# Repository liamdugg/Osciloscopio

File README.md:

# Osciloscopio

Proyecto TDII - 2022

Osciloscopio para señales audibles

Integrantes
  - Contreras, Nahuel
  - Duggan, Liam
  - Ochoa, David

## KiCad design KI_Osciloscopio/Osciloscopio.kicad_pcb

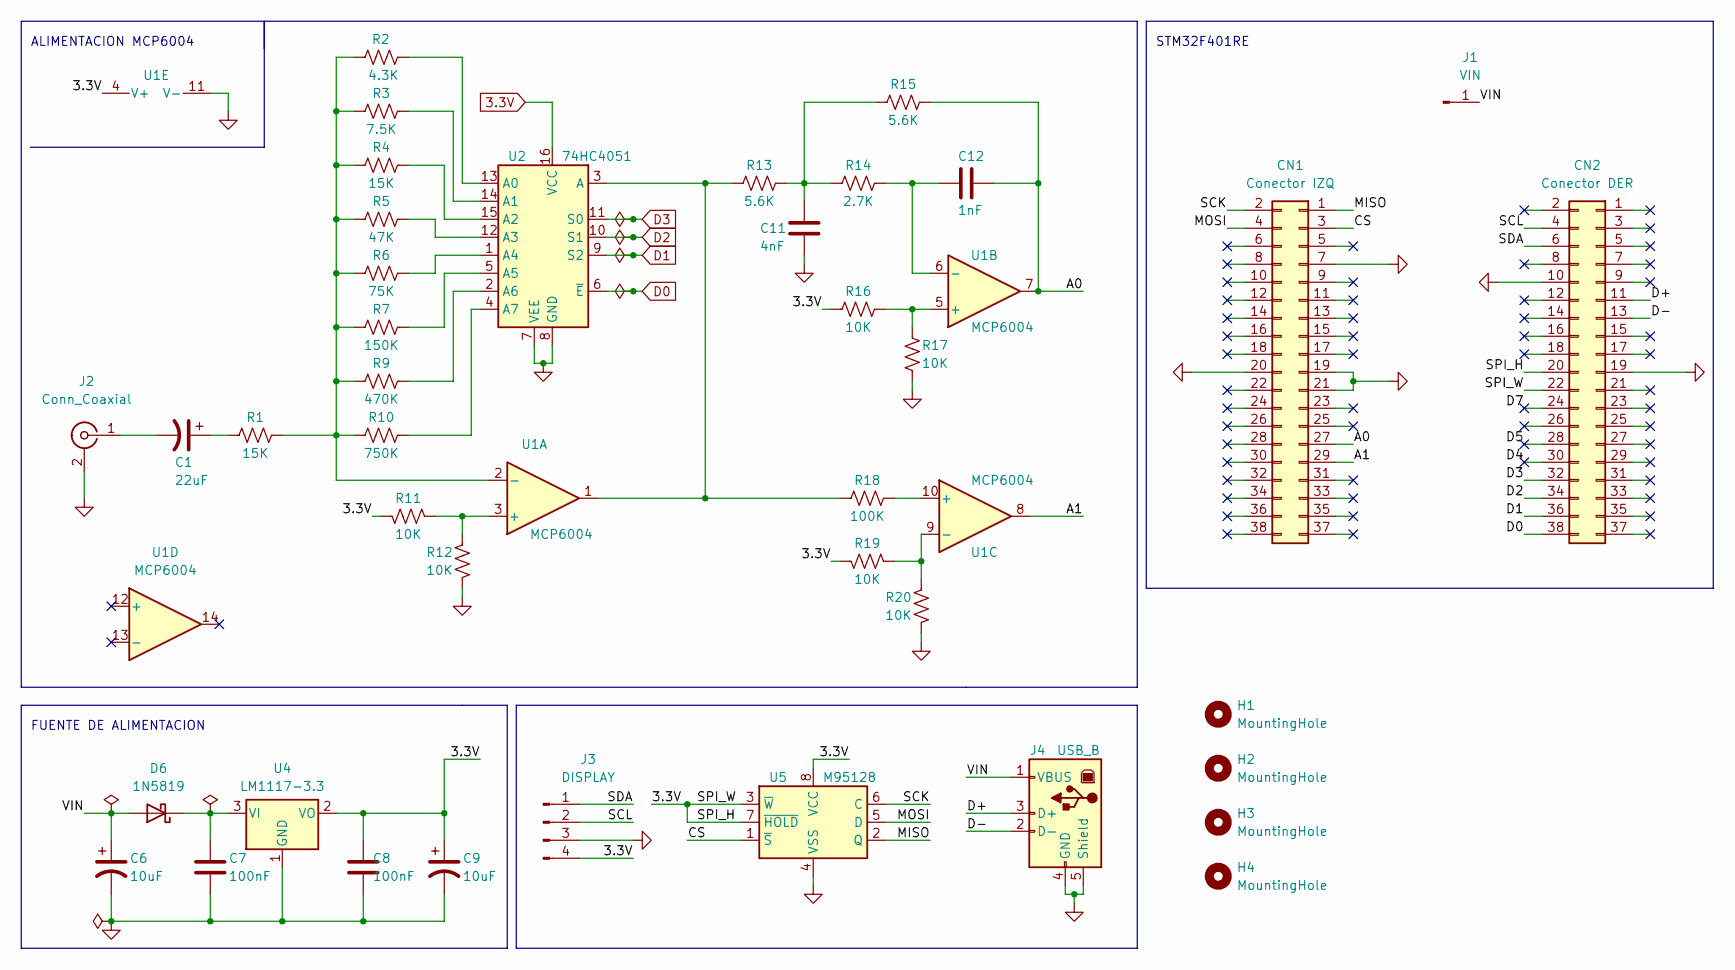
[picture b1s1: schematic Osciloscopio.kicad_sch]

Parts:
C1: 22uF; C_Radial_D6.3mm_H11.0mm_P2.50mm
C6, C9: 10uF; C_Radial_D6.3mm_H11.0mm_P2.50mm
C7, C8: 100nF; C_Disc_D5.0mm_W2.5mm_P2.50mm
C11: 4nF; C_Disc_D5.0mm_W2.5mm_P2.50mm
C12: 1nF; C_Disc_D5.0mm_W2.5mm_P2.50mm
CN1: Conector IZQ; PinSocket_2x19_P2.54mm_Vertical
CN2: Conector DER; PinSocket_2x19_P2.54mm_Vertical
D6: 1N5819; D_DO-41_SOD81_P10.16mm_Horizontal
H1, H2, H3, H4: MountingHole; MountingHole_2.5mm
J1: VIN; PinHeader_1x01_P2.54mm_Vertical
J2: Conn_Coaxial; BNC_Amphenol_B6252HB-NPP3G-50_Horizontal
J3: DISPLAY; PinHeader_1x04_P2.54mm_Vertical
J4: USB_B; USB_B_OST_USB-B1HSxx_Horizontal
R1, R4: 15K; R_Axial_DIN0207_L6.3mm_D2.5mm_P10.16mm_Horizontal
R2: 4.3K; R_Axial_DIN0207_L6.3mm_D2.5mm_P10.16mm_Horizontal
R3: 7.5K; R_Axial_DIN0207_L6.3mm_D2.5mm_P10.16mm_Horizontal
R5: 47K; R_Axial_DIN0207_L6.3mm_D2.5mm_P10.16mm_Horizontal
R6: 75K; R_Axial_DIN0207_L6.3mm_D2.5mm_P10.16mm_Horizontal
R7: 150K; R_Axial_DIN0207_L6.3mm_D2.5mm_P10.16mm_Horizontal
R9: 470K; R_Axial_DIN0207_L6.3mm_D2.5mm_P10.16mm_Horizontal
R10: 750K; R_Axial_DIN0207_L6.3mm_D2.5mm_P10.16mm_Horizontal
R11, R12, R16, R17, R19, R20: 10K; R_Axial_DIN0207_L6.3mm_D2.5mm_P10.16mm_Horizontal
R13, R15: 5.6K; R_Axial_DIN0207_L6.3mm_D2.5mm_P10.16mm_Horizontal
R14: 2.7K; R_Axial_DIN0207_L6.3mm_D2.5mm_P10.16mm_Horizontal
R18: 100K; R_Axial_DIN0207_L6.3mm_D2.5mm_P10.16mm_Horizontal
U1: MCP6004
U2: 74HC4051; DIP-16_W7.62mm
U4: LM1117-3.3; TO-220-3_Vertical
U5: M95128; DIP-8_W7.62mm

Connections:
3.3V: C8.1, C9.1, CN2.20, CN2.22, J3.4, R11.2, R16.2, R19.2, U1.4 (V+), U2.16 (VCC), U4.2 (VO), U5.3 (~W), U5.7 (~HOLD), U5.8 (VCC)
/A0: C12.1, CN1.27, R15.1, U1.7
/A1: CN1.29, U1.8
/CS: CN1.3, U5.1 (~S)
/D4: CN2.30
/D5: CN2.28
/D7: CN2.24
/D+: CN2.11, J4.3 (D+)
/D-: CN2.13, J4.2 (D-)
/MISO: CN1.1, U5.2 (Q)
/MOSI: CN1.4, U5.5 (D)
/SCK: CN1.2, U5.6 (C)
/SCL: CN2.4, J3.2
/SDA: CN2.6, J3.1
/VIN: C6.1, D6.2 (A), J1.1, J4.1 (VBUS)
D0: CN2.38, U2.6 (~E)
D1: CN2.36, U2.9 (S2)
D2: CN2.34, U2.10 (S1)
D3: CN2.32, U2.11 (S0)
GND: C6.2, C7.2, C8.2, C9.2, C11.1, CN1.7, CN1.19, CN1.20, CN1.21, CN2.10, CN2.19, J2.2 (Ext), J3.3, J4.4 (GND), J4.5 (Shield), R12.2, R17.2, R20.2, U1.11 (V-), U2.7 (VEE), U2.8 (GND), U4.1 (GND), U5.4 (VSS)
unnamed: C1.1, R1.2
unnamed: C1.2, J2.1 (In)
unnamed: C7.1, D6.1 (K), U4.3 (VI)
unnamed: C11.2, R13.1, R14.2, R15.2
unnamed: C12.2, R14.1, U1.6 (-)
unnamed: R1.1, R2.1, R3.2, R4.2, R5.2, R6.2, R7.2, R9.2, R10.2, U1.2 (-)
unnamed: R2.2, U2.13 (A0)
unnamed: R3.1, U2.14 (A1)
unnamed: R4.1, U2.15 (A2)
unnamed: R5.1, U2.12 (A3)
unnamed: R6.1, U2.1 (A4)
unnamed: R7.1, U2.5 (A5)
unnamed: R9.1, U2.2 (A6)
unnamed: R10.1, U2.4 (A7)
unnamed: R11.1, R12.1, U1.3 (+)
unnamed: R13.2, R18.2, U1.1, U2.3 (A)
unnamed: R16.1, R17.1, U1.5 (+)
unnamed: R18.1, U1.10 (+)
unnamed: R19.1, R20.1, U1.9 (-)

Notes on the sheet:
STM32F401RE
ALIMENTACION MCP6004
FUENTE DE ALIMENTACION

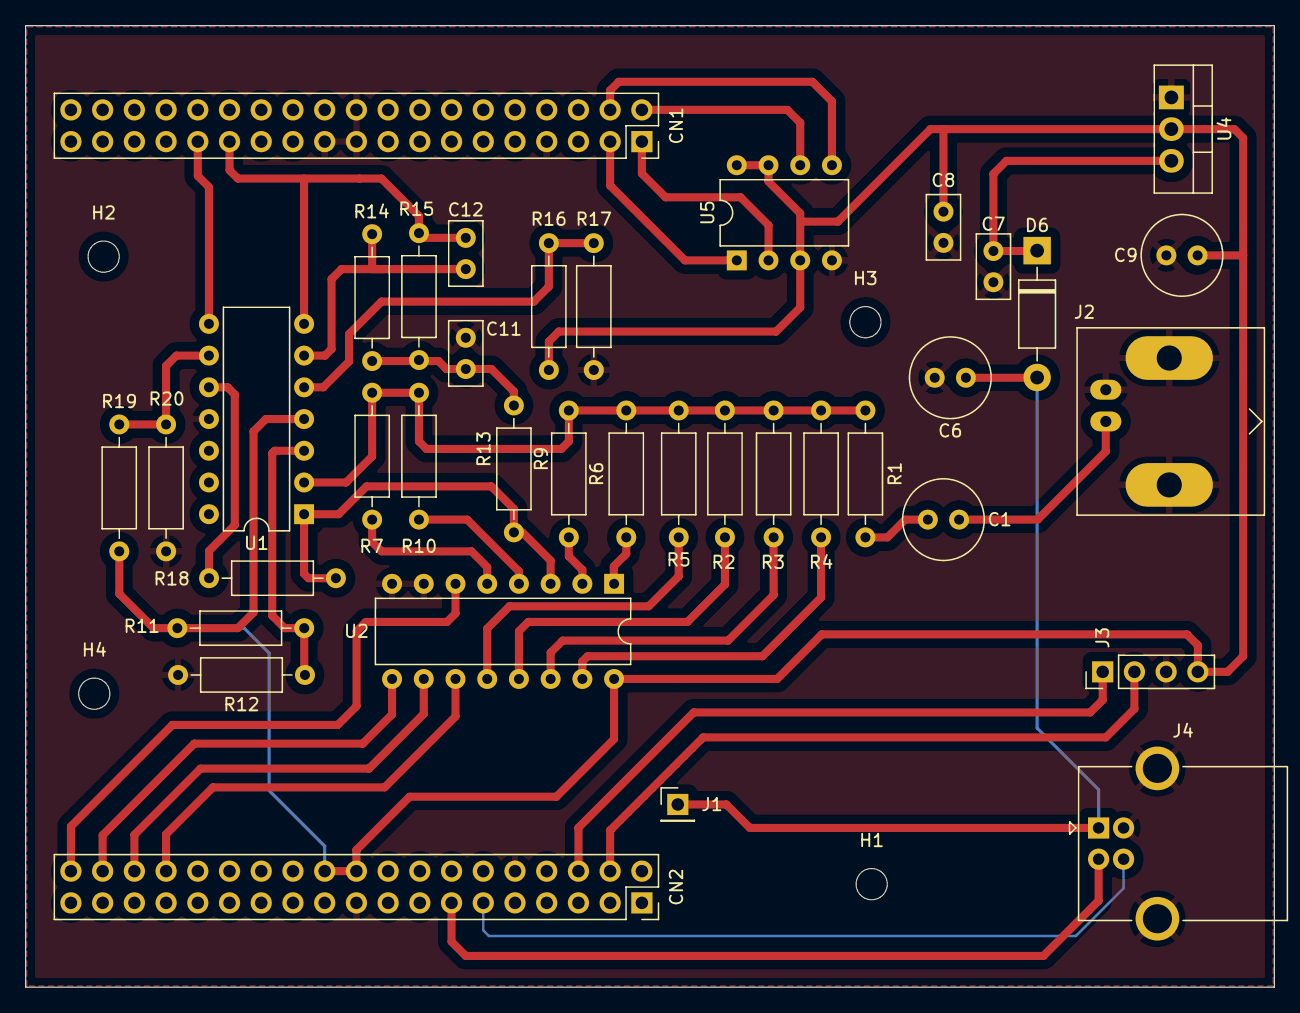
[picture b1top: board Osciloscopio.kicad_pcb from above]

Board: 2 copper layers, 100.0 x 77.0 mm, 41 parts (0 on the bottom side), 36 nets.

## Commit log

2022-10-18 Add archivos de Kicad
2022-10-18 ADD Proyecto ST
2022-10-19 Termine circuitos en kicad
    Los dejé como estaban en las imagenes, osea mismos valores y componentes. Hay que ver despues si lo modificamos o no
2022-10-19 Cambie labels que estaban mal
2022-10-21 Agregando la biblioteca DSP
2022-10-21 Agregando carpeta de informe
2022-10-21 Informe G4
2022-10-21 Informe
2022-10-21 Corrigiendo error de Imagen
2022-10-21 Agregando la carpeta Informe
2022-10-22 Modificaciones del informe
2022-10-22 Informe Inicial
2022-10-23 Incorporacion de un LPF Multiple Feedback
2022-10-25 Cambie regulador de tension 7805
2022-10-28 Circuito acondicionador de señal terminado
2022-10-28 Circuito Acondicionador terminado
2022-10-28 Pines AD0 AD1 y I2C1
2022-10-30 Esquematico terminado
2022-11-09 Agregue Pines para ST en la placa
2022-11-09 Agregue algunos footprints
2022-11-11 Complete la BOM con los footprints
2022-11-25 Cambie el circuito de alimentacion
2022-12-11 Termine PCB
2022-12-15 Plaquita
2022-12-15 La concha de tu madre
2022-12-16 Kicad Terminado
2023-02-03 nada importante
2023-02-03 Pruebas ADC
2023-02-03 Agregue funciones de RTOS
2023-02-03 pruebas trigger
2023-02-04 Prueba Trigger
2023-02-04 trigger anda 2.0
2023-02-04 Prueba de trigger con un generador
2023-02-05 cambie nombres de func y agregue una func
2023-02-05 desplazamiento trigger
2023-02-09 Prueba con el hardware OK
2023-02-09 Puerto GPIO corregido
2023-02-09 Actualizacion Escala
2023-02-10 Correccion Mux y actualizacion de la frecuencia
2023-02-10 Agregando USB+ADC
2023-02-16 Corrección de trigger para USB
2023-02-18 frecuencia baja de muestreo
2023-02-18 calculo de frecuencia de muestreo
2023-02-19 prueba de frecuencia de muestreo parte 1
2023-02-20 frecuencias altas funcionando
2023-02-20 Agregando interfaz grafica de Qt
2023-02-22 RMS y freq andando
2023-02-23 Encoder + Trigge + Fs + At/Gan (funcionando correctamente)
2023-02-23 archivos a copiar despues de abrir IOC
2023-02-26 Ultima versión de adc timer
2023-02-27 Qt completo
2023-02-28 Ultimo commit
2023-02-28 final
